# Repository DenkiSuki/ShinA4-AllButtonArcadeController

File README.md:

# ShinA4-AllButtonArcadeController
Repo for ShinA4, a custom 3DPrinted All Button Arcade Controller

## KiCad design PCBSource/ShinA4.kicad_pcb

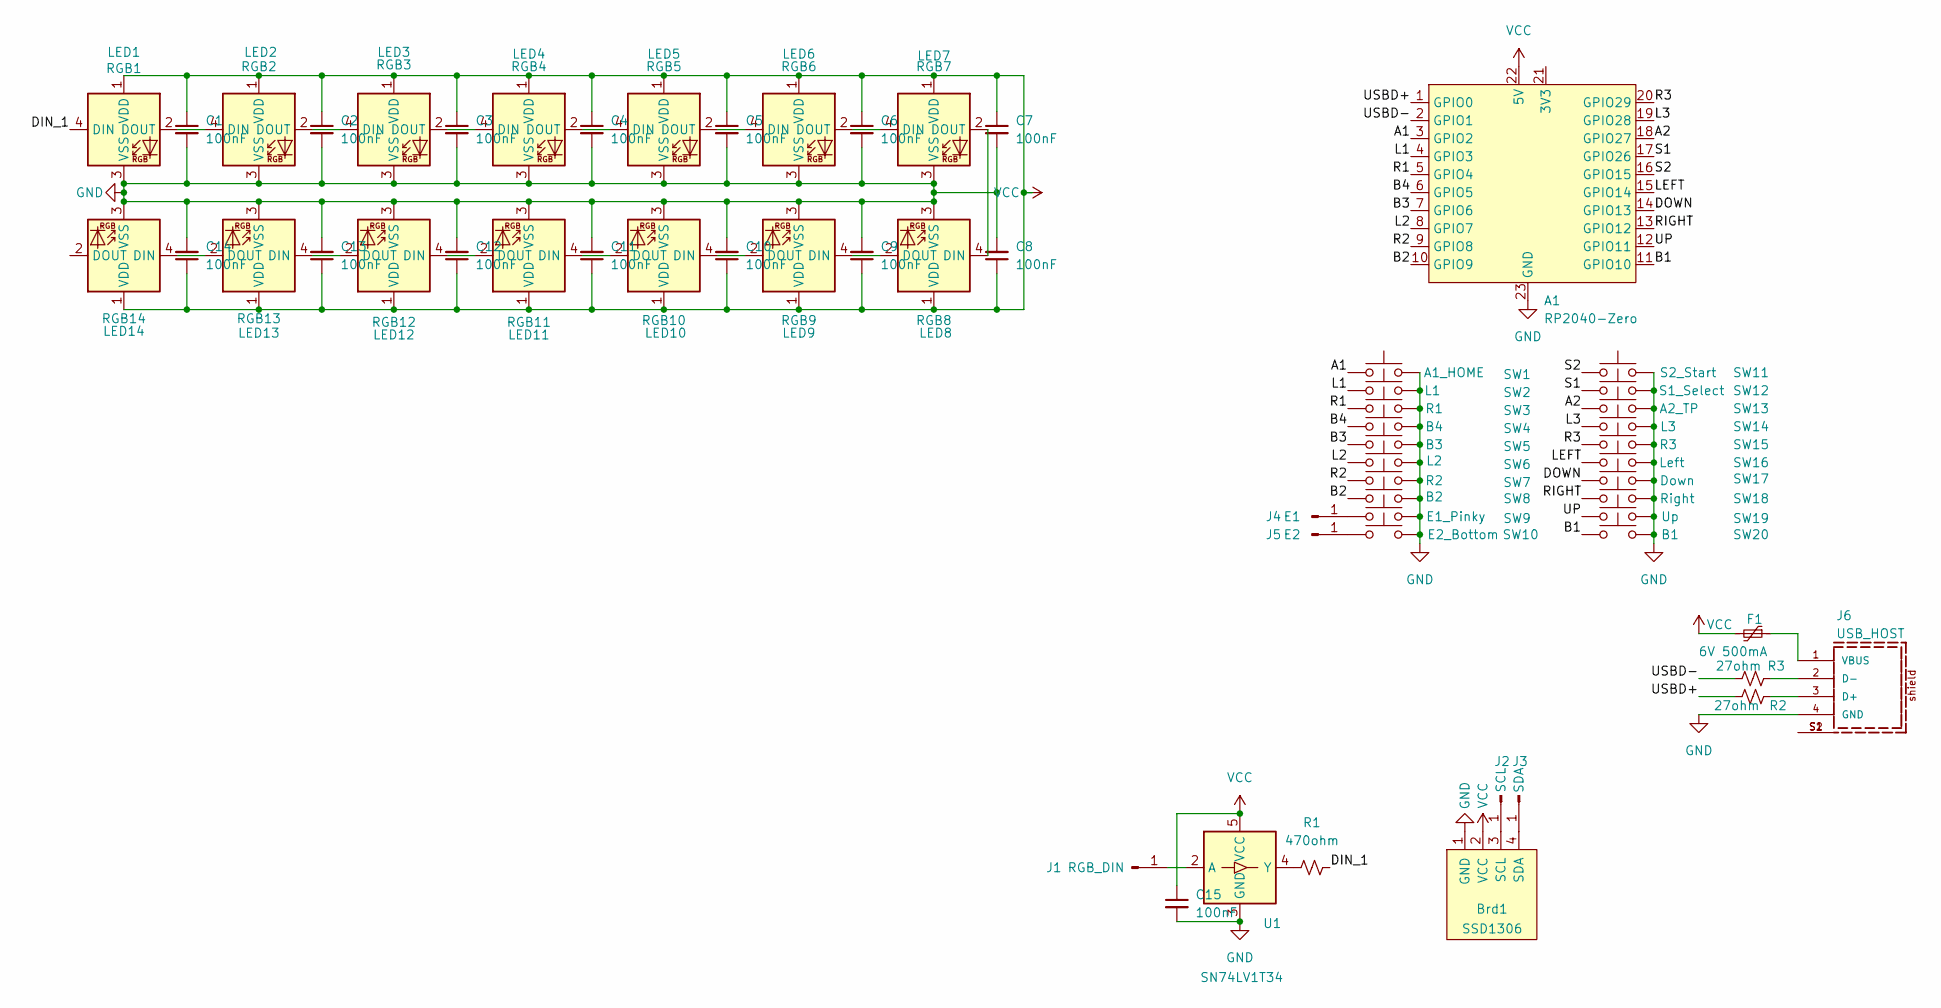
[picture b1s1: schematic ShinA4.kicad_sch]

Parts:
A1: RP2040-Zero; RP2040-Zero_BottomCu
Brd1: SSD1306; Display_128x64_096_I2C_Modified
C1, C2, C3, C4, C5, C6, C7, C8, C9, C10, C11, C12, C13, C14, C15: 100nF; C_0603_1608Metric_Pad1.08x0.95mm_HandSolder
F1: 6V 500mA; Fuse_0805_2012Metric_Pad1.15x1.40mm_HandSolder
J1: RGB_DIN; TestPoint_THTPad_D1.0mm_Drill0.5mm
J2: SCL; TestPoint_THTPad_D1.0mm_Drill0.5mm
J3: SDA; TestPoint_THTPad_D1.0mm_Drill0.5mm
J4: E1; TestPoint_THTPad_D1.0mm_Drill0.5mm
J5: E2; TestPoint_THTPad_D1.0mm_Drill0.5mm
J6: USB_HOST; 61400416021; PART-NUMBER 61400416021
LED1: RGB1; YS-SK6812MINI-E
LED2: RGB2; YS-SK6812MINI-E
LED3: RGB3; YS-SK6812MINI-E
LED4: RGB4; YS-SK6812MINI-E
LED5: RGB5; YS-SK6812MINI-E
LED6: RGB6; YS-SK6812MINI-E
LED7: RGB7; YS-SK6812MINI-E
LED8: RGB8; YS-SK6812MINI-E
LED9: RGB9; YS-SK6812MINI-E
LED10: RGB10; YS-SK6812MINI-E
LED11: RGB11; YS-SK6812MINI-E
LED12: RGB12; YS-SK6812MINI-E
LED13: RGB13; YS-SK6812MINI-E
LED14: RGB14; YS-SK6812MINI-E
R1: 470ohm; R_0603_1608Metric_Pad0.98x0.95mm_HandSolder
R2, R3: 27ohm; R_0603_1608Metric_Pad0.98x0.95mm_HandSolder
SW1: A1_HOME; Kailh_socket_PG1350_V1+2
SW2: L1; Kailh_socket_PG1350_V1+2
SW3: R1; Kailh_socket_PG1350_V1+2
SW4: B4; Kailh_socket_PG1350_V1+2
SW5: B3; Kailh_socket_PG1350_V1+2
SW6: L2; Kailh_socket_PG1350_V1+2
SW7: R2; Kailh_socket_PG1350_V1+2
SW8: B2; Kailh_socket_PG1350_V1+2
SW9: E1_Pinky; Kailh_socket_PG1350_V1+2
SW10: E2_Bottom; Kailh_socket_PG1350_V1+2
SW11: S2_Start; Kailh_socket_PG1350_V1+2
SW12: S1_Select; Kailh_socket_PG1350_V1+2
SW13: A2_TP; Kailh_socket_PG1350_V1+2
SW14: L3; Kailh_socket_PG1350_V1+2
SW15: R3; Kailh_socket_PG1350_V1+2
SW16: Left; Kailh_socket_PG1350_V1+2
SW17: Down; Kailh_socket_PG1350_V1+2
SW18: Right; Kailh_socket_PG1350_V1+2
SW19: Up; Kailh_socket_PG1350_V1+2
SW20: B1; Kailh_socket_PG1350_V1+2
U1: SN74LV1T34; SOT-23-5

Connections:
/A1: A1.3 (GPIO2), SW1.1
/A2: A1.18 (GPIO27), SW13.1
/B1: A1.11 (GPIO10), SW20.1
/B2: A1.10 (GPIO9), SW8.1
/B3: A1.7 (GPIO6), SW5.1
/B4: A1.6 (GPIO5), SW4.1
/DIN_1: LED1.4 (DIN), R1.2
/DOWN: A1.14 (GPIO13), SW17.1
/L1: A1.4 (GPIO3), SW2.1
/L2: A1.8 (GPIO7), SW6.1
/L3: A1.19 (GPIO28), SW14.1
/LEFT: A1.15 (GPIO14), SW16.1
/R1: A1.5 (GPIO4), SW3.1
/R2: A1.9 (GPIO8), SW7.1
/R3: A1.20 (GPIO29), SW15.1
/RIGHT: A1.13 (GPIO12), SW18.1
/S1: A1.17 (GPIO26), SW12.1
/S2: A1.16 (GPIO15), SW11.1
/UP: A1.12 (GPIO11), SW19.1
/USBD+: A1.1 (GPIO0), R2.2
/USBD-: A1.2 (GPIO1), R3.2
GND: A1.23 (GND), Brd1.1 (GND), C1.2, C2.2, C3.2, C4.2, C5.2, C6.2, C7.2, C8.2, C9.2, C10.2, C11.2, C12.2, C13.2, C14.2, C15.2, J6.4 (GND), LED1.3 (VSS), LED2.3 (VSS), LED3.3 (VSS), LED4.3 (VSS), LED5.3 (VSS), LED6.3 (VSS), LED7.3 (VSS), LED8.3 (VSS), LED9.3 (VSS), LED10.3 (VSS), LED11.3 (VSS), LED12.3 (VSS), LED13.3 (VSS), LED14.3 (VSS), SW1.2, SW2.2, SW3.2, SW4.2, SW5.2, SW6.2, SW7.2, SW8.2, SW9.2, SW10.2, SW11.2, SW12.2, SW13.2, SW14.2, SW15.2, SW16.2, SW17.2, SW18.2, SW19.2, SW20.2, U1.3 (GND)
unnamed: Brd1.3 (SCL), J2.1
unnamed: Brd1.4 (SDA), J3.1
unnamed: J1.1, U1.2 (A)
unnamed: J4.1, SW9.1
unnamed: J5.1, SW10.1
unnamed: J6.3 (D+), R2.1
unnamed: J6.2 (D-), R3.1
unnamed: J6.S1, J6.S2
unnamed: F1.1, J6.1 (VBUS)
unnamed: LED1.2 (DOUT), LED2.4 (DIN)
unnamed: LED2.2 (DOUT), LED3.4 (DIN)
unnamed: LED3.2 (DOUT), LED4.4 (DIN)
unnamed: LED4.2 (DOUT), LED5.4 (DIN)
unnamed: LED5.2 (DOUT), LED6.4 (DIN)
unnamed: LED6.2 (DOUT), LED7.4 (DIN)
unnamed: LED7.2 (DOUT), LED8.4 (DIN)
unnamed: LED8.2 (DOUT), LED9.4 (DIN)
unnamed: LED9.2 (DOUT), LED10.4 (DIN)
unnamed: LED10.2 (DOUT), LED11.4 (DIN)
unnamed: LED11.2 (DOUT), LED12.4 (DIN)
unnamed: LED12.2 (DOUT), LED13.4 (DIN)
unnamed: LED13.2 (DOUT), LED14.4 (DIN)
unnamed: R1.1, U1.4 (Y)
VCC: A1.22 (5V), Brd1.2 (VCC), C1.1, C2.1, C3.1, C4.1, C5.1, C6.1, C7.1, C8.1, C9.1, C10.1, C11.1, C12.1, C13.1, C14.1, C15.1, F1.2, LED1.1 (VDD), LED2.1 (VDD), LED3.1 (VDD), LED4.1 (VDD), LED5.1 (VDD), LED6.1 (VDD), LED7.1 (VDD), LED8.1 (VDD), LED9.1 (VDD), LED10.1 (VDD), LED11.1 (VDD), LED12.1 (VDD), LED13.1 (VDD), LED14.1 (VDD), U1.5 (VCC)

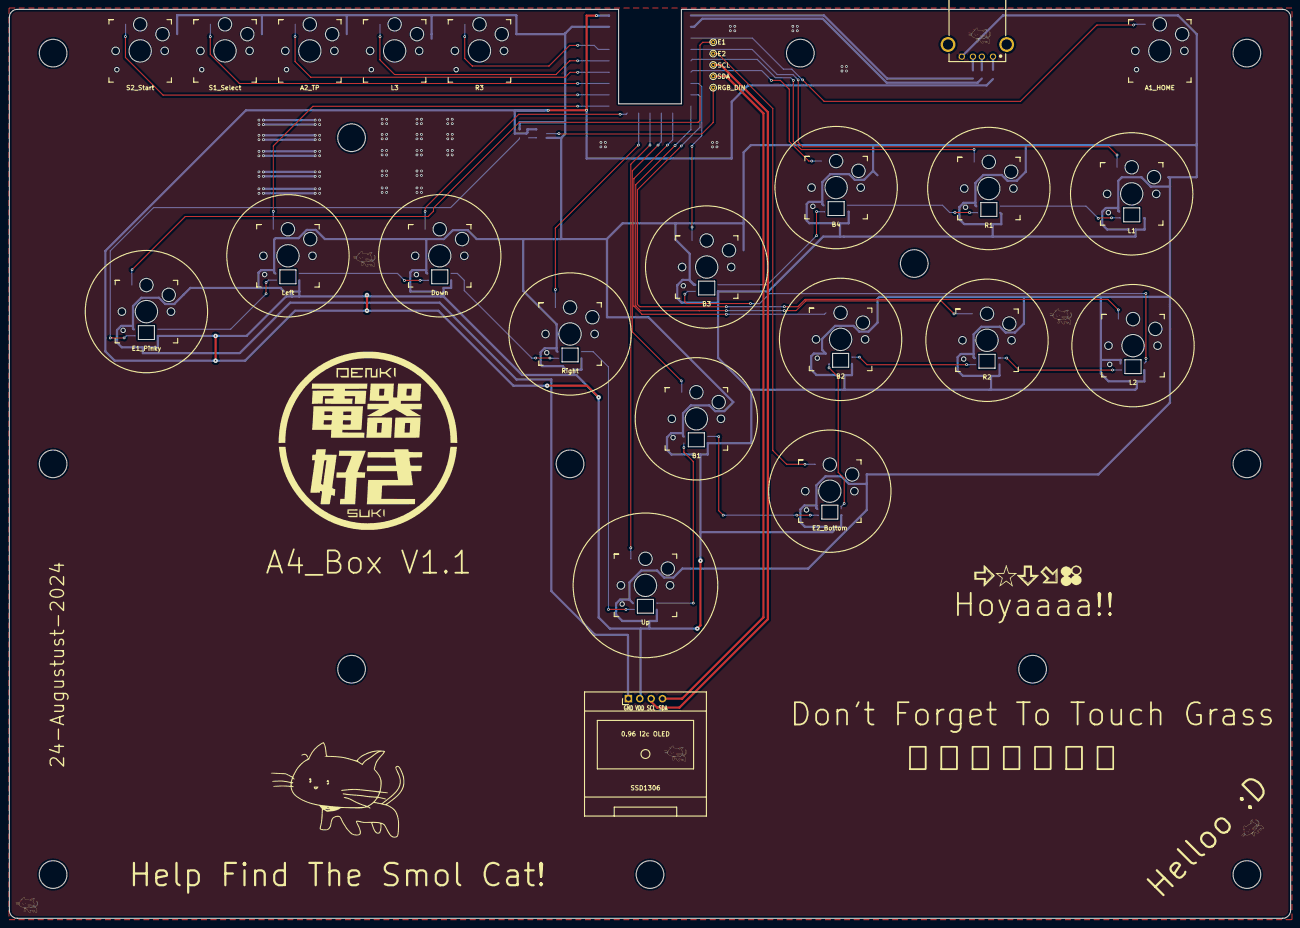
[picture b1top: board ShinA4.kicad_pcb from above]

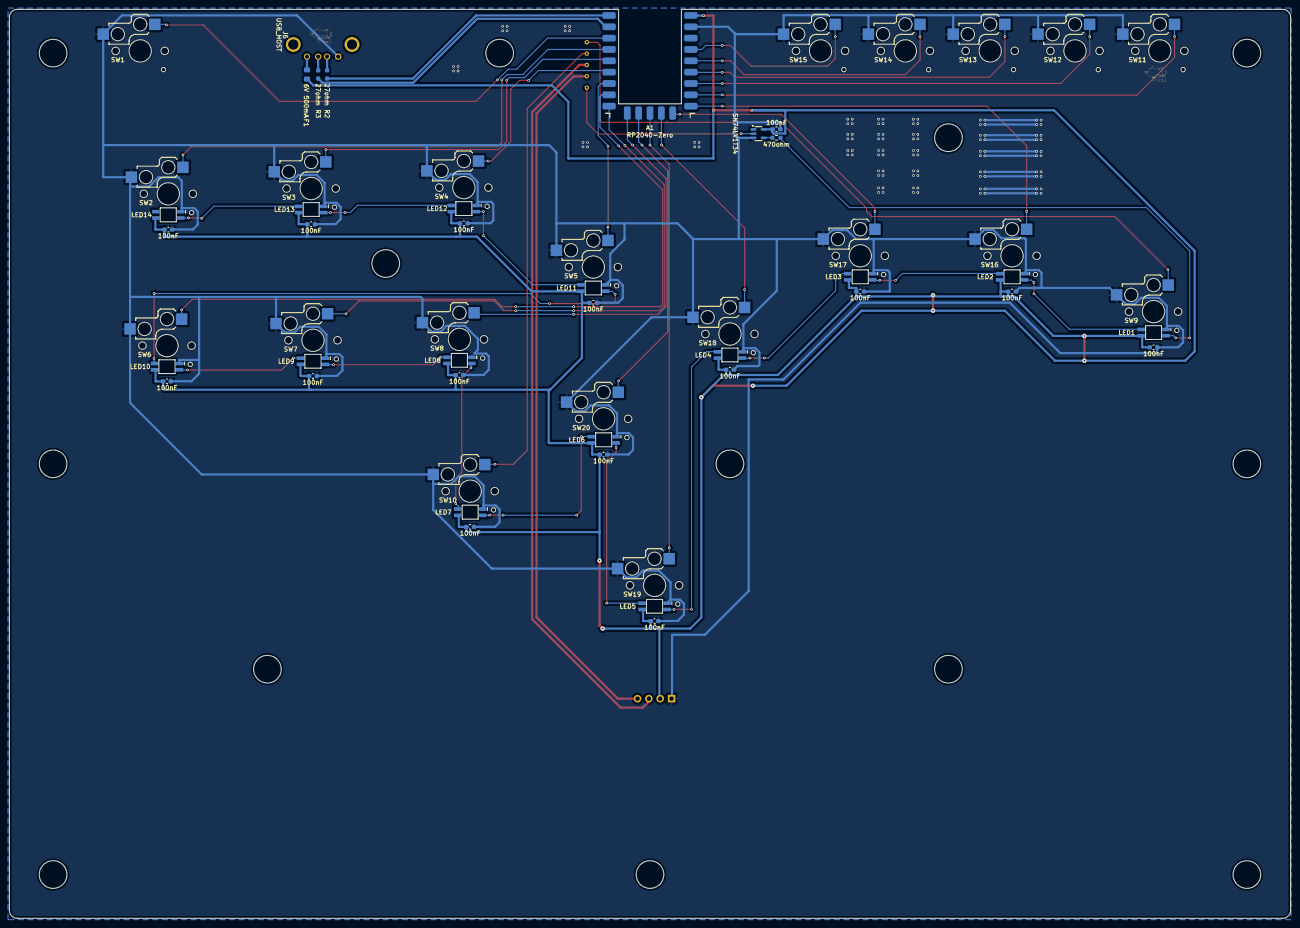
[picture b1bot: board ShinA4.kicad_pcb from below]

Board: 2 copper layers, 287.0 x 203.6 mm, 62 parts (34 on the bottom side), 46 nets.

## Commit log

2024-10-27 Initial Commit
    Adding all project files that available until now, the 3d file are tested, the pcb file should be work, because the previous version is working, and the change is only on the capacitor size for sk681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
2024-10-27 added render picture
2024-10-29 Update README.md
    adding layout
